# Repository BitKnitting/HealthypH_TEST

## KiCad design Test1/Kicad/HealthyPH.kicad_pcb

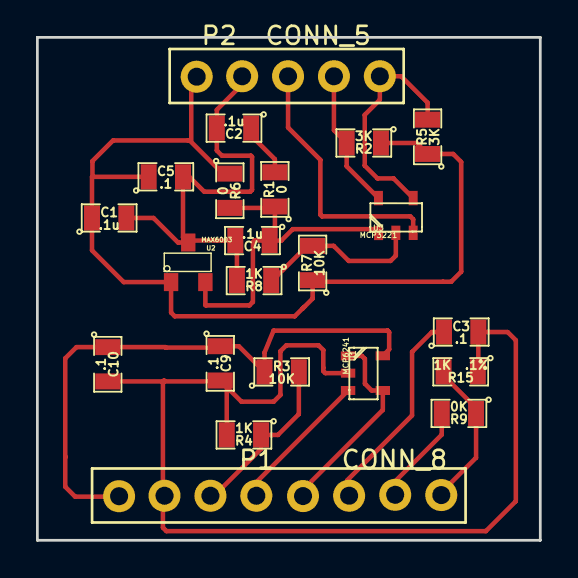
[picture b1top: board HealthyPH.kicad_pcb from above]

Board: 2 copper layers, 27.9 x 27.9 mm, 22 parts (0 on the bottom side), 16 nets.

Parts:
C1, C2, C4: .1u; SM0805
C3, C5, C9, C10: .1; SM0805
P1: CONN_8; LB_CONN_8
P2: CONN_5; LB_CONN_5
R1, R6: 0; SM0805
R2, R5: 3K; SM0805
R3, R7: 10K; SM0805
R4, R8: 1K; SM0805
R9: 0K; SM0805
R15: 1K .1%; SM0805
U1: MCP6241; LB_MCP3221
U2: MAX6003; LB_SOT23
U3: MCP3221; LB_MCP3221

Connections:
/Digital Access/AIN: P2.3, U3.3
/Digital Access/GND_WallWart: C1.2, C2.2, C4.2, C5.2, P2.2, R8.2, U2.3
/Digital Access/SCL: P2.4, R2.2, U3.5
/Digital Access/SDA: P2.5, R5.2, U3.4
/Digital Access/V+_WallWart: C1.1, C5.1, P2.1, R2.1, R5.1, R6.1, R7.1, U2.1
/Temperature/GND_WallWart: C3.2, C9.2, C10.2, P1.2, R4.2, R15.1, U1.2
/Temperature/Therm_AIN: P1.8, R9.1, R15.2
/Temperature/Therm_IN: P1.7, R9.2
/Temperature/V+_WallWart_Therm: C3.1, P1.6
/pH/V+_WallWart: C9.1, C10.1, P1.1, R3.1, U1.5
/pH/pH_AIN: P1.5, U1.1, U1.4
/pH/pH_Probe_VGND: P1.3, R3.2, R4.1
/pH/pH_Probe_VIN: P1.4, U1.3
unnamed: C2.1, R1.2
VGND: R7.2, R8.1, U3.2
VREF: C4.1, R1.1, R6.2, U2.2, U3.1
